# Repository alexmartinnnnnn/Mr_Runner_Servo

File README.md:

# Mr_Runner_Servo

These are two programs which can be used in conjunction to control the Mr. Runner quadrupedal robot.

The code could be modified to control other 8 jointed robots. The required electronics are a
computer, microcontroller, PCB to power servos, and a serial connection.

https://hackaday.io/project/8843-mr-runner

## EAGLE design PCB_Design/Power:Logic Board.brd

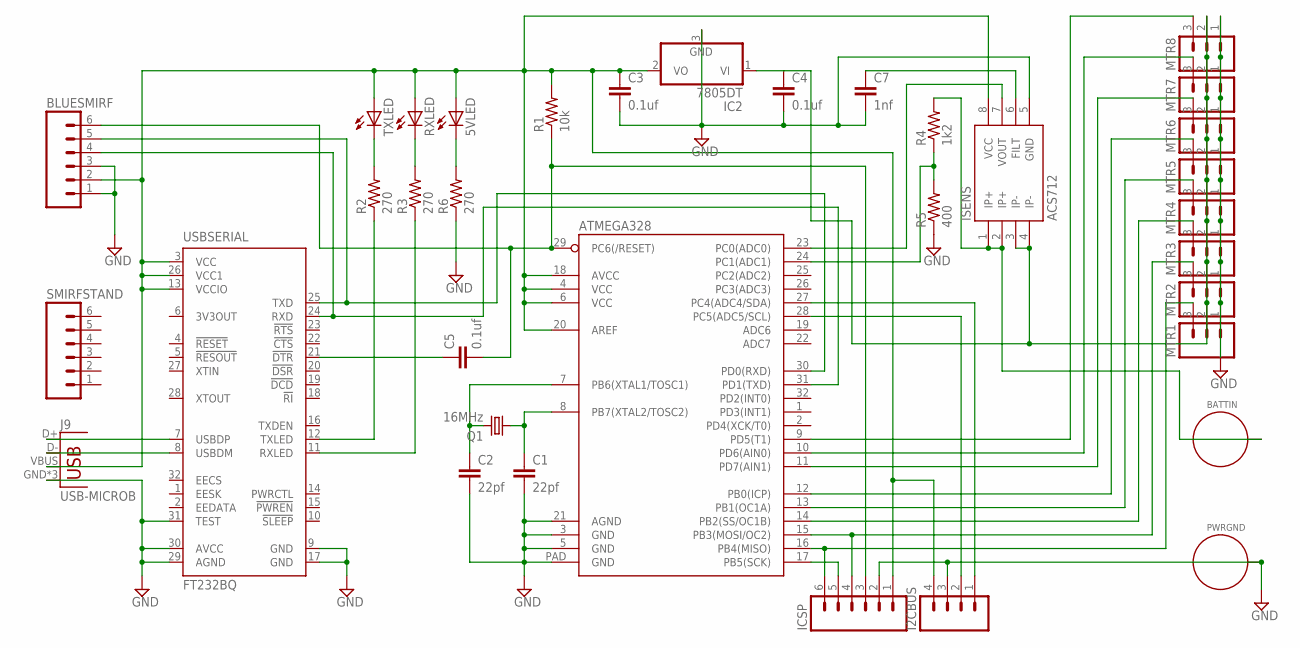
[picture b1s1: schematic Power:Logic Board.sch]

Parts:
5VLED: LEDCHIPLED_0805; CHIPLED_0805
ATMEGA328: ATMEGA328P_MLFMLF32; MLF32-PAD
BATTIN: STANDOFF_ELECTRICAL; STANDOFF-ELECTRICAL
BLUESMIRF: M06NO_SILK_YES_STOP; 1X06_NO_SILK_YES_STOP
C1, C2: 22pf; C0805
C3, C4, C5: 0.1uf; C0805
C7: 1nf; C0805
I2CBUS: M04NO_SILK_ALL_ROUND; 1X04_NO_SILK_ALL_ROUND
IC2: 7805DT; TO252
ICSP: M06NO_SILK_YES_STOP; 1X06_NO_SILK_YES_STOP
ISENS: ACS712; SO08
J9: USB-MICROB
MTR1, MTR2, MTR3, MTR4, MTR5, MTR6, MTR7, MTR8: M03PTH; 1X03
PWRGND: STANDOFF_ELECTRICAL; STANDOFF-ELECTRICAL
Q1: 16MHz; HC49U-V
R1: 10k; 0805
R2, R3, R6: 270; 0805
R4: 1k2; 0805
R5: 400; 0805
RXLED: LEDCHIPLED_0805; CHIPLED_0805
SMIRFSTAND: M06NO_SILK_YES_STOP; 1X06_NO_SILK_YES_STOP
TXLED: LEDCHIPLED_0805; CHIPLED_0805
USBSERIAL: FT232BQ; QFN32

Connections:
GND: ATMEGA328.3 (GND), ATMEGA328.5 (GND), ATMEGA328.21 (AGND), ATMEGA328.PAD (GND), BLUESMIRF.1, BLUESMIRF.3, C1.2, C2.2, C3.2, C4.2, C7.2, I2CBUS.3, IC2.3 (GND), ICSP.2, ISENS.5 (GND), J9.GND, J9.MT1 (GND), J9.MT2 (GND), MTR1.1, MTR2.1, MTR3.1, MTR4.1, MTR5.1, MTR6.1, MTR7.1, MTR8.1, PWRGND.P1, R5.1, R6.1, USBSERIAL.9 (GND), USBSERIAL.17 (GND), USBSERIAL.29 (AGND), USBSERIAL.30 (AVCC), USBSERIAL.31 (TEST)
unnamed: J9.D+, USBSERIAL.7 (USBDP)
unnamed: ATMEGA328.31 (PD1(TXD)), BLUESMIRF.4, USBSERIAL.24 (RXD)
unnamed: J9.D-, USBSERIAL.8 (USBDM)
unnamed: 5VLED.A, ATMEGA328.4 (VCC), ATMEGA328.6 (VCC), ATMEGA328.18 (AVCC), ATMEGA328.20 (AREF), BLUESMIRF.2, C3.1, I2CBUS.4, IC2.2 (VO), ICSP.1, ISENS.8 (VCC), J9.VBUS, R1.2, RXLED.A, TXLED.A, USBSERIAL.3 (VCC), USBSERIAL.13 (VCCIO), USBSERIAL.26 (VCC1)
unnamed: ATMEGA328.14 (PB2(SS/OC1B)), MTR3.3
unnamed: ATMEGA328.23 (PC0(ADC0)), ISENS.7 (VOUT)
unnamed: ATMEGA328.8 (PB7(XTAL2/TOSC2)), C1.1, Q1.1
unnamed: ATMEGA328.9 (PD5(T1)), MTR8.3
unnamed: ATMEGA328.13 (PB1(OC1A)), MTR4.3
unnamed: ATMEGA328.17 (PB5(SCK)), ICSP.5
unnamed: ATMEGA328.12 (PB0(ICP)), MTR5.3
unnamed: ATMEGA328.16 (PB4(MISO)), ICSP.6, MTR1.3
unnamed: ATMEGA328.15 (PB3(MOSI/OC2)), ICSP.4, MTR2.3
unnamed: R2.2, TXLED.C
unnamed: ATMEGA328.7 (PB6(XTAL1/TOSC1)), C2.1, Q1.2
unnamed: R2.1, USBSERIAL.12 (TXLED)
unnamed: R3.2, RXLED.C
unnamed: R3.1, USBSERIAL.11 (RXLED)
unnamed: ATMEGA328.11 (PD7(AIN1)), MTR6.3
unnamed: ATMEGA328.29 (PC6(/RESET)), BLUESMIRF.6, C5.2, ICSP.3, R1.1
unnamed: C7.1, ISENS.6 (FILT)
unnamed: C4.1, IC2.1 (VI), ISENS.3 (IP-), ISENS.4 (IP-), MTR1.2, MTR2.2, MTR3.2, MTR4.2, MTR5.2, MTR6.2, MTR7.2, MTR8.2
unnamed: ATMEGA328.24 (PC1(ADC1)), R4.1, R5.2
unnamed: ATMEGA328.10 (PD6(AIN0)), MTR7.3
unnamed: BATTIN.P1, ISENS.1 (IP+), ISENS.2 (IP+), R4.2
unnamed: ATMEGA328.30 (PD0(RXD)), BLUESMIRF.5, USBSERIAL.25 (TXD)
unnamed: C5.1, USBSERIAL.21 (!DTR)
unnamed: ATMEGA328.28 (PC5(ADC5/SCL)), I2CBUS.2
unnamed: ATMEGA328.27 (PC4(ADC4/SDA)), I2CBUS.1
unnamed: 5VLED.C, R6.2

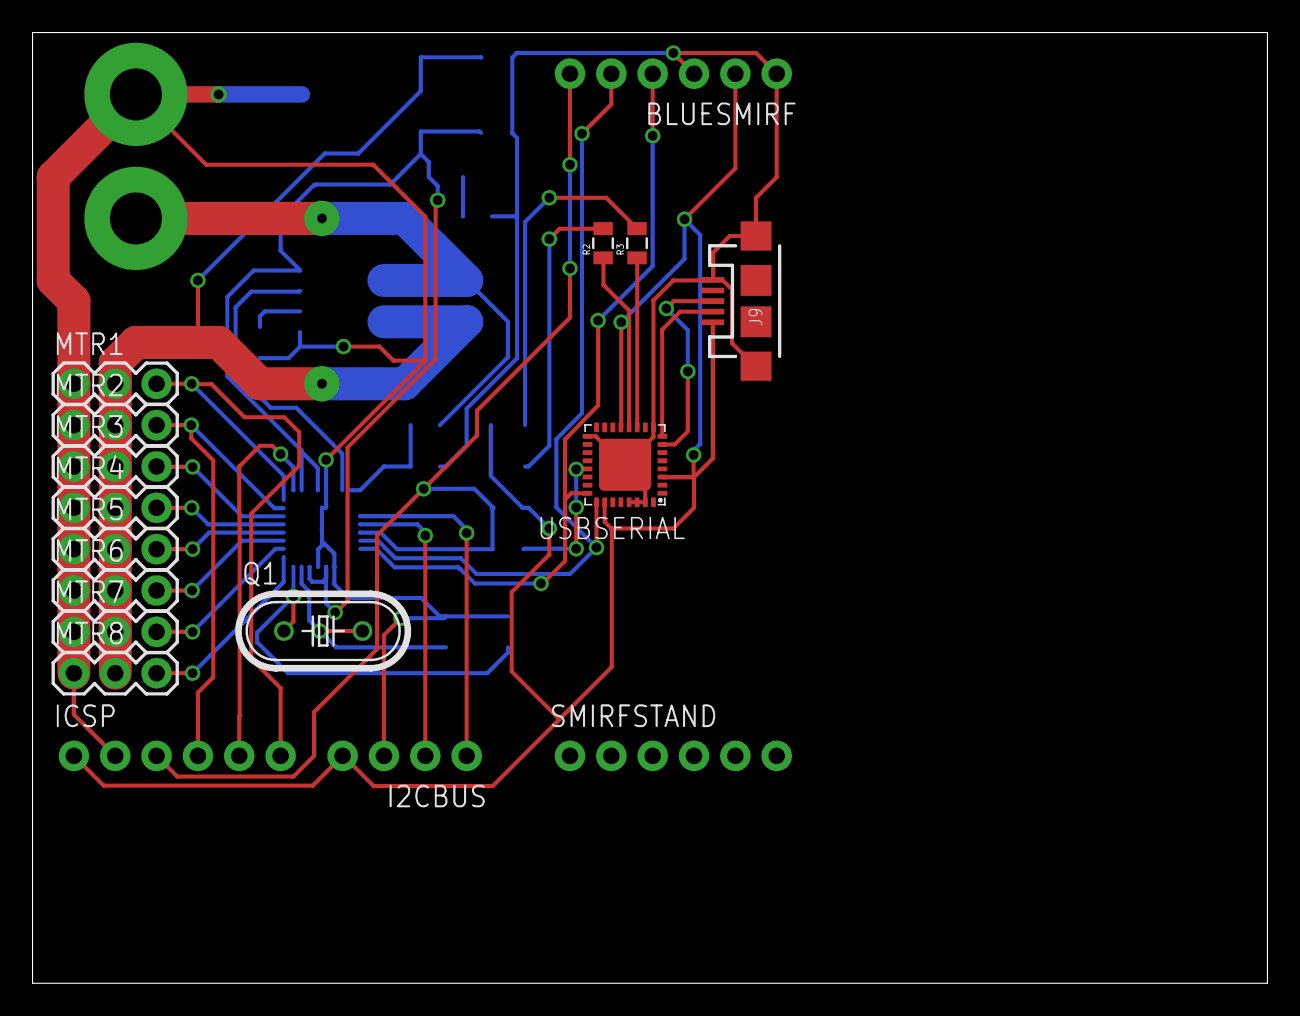
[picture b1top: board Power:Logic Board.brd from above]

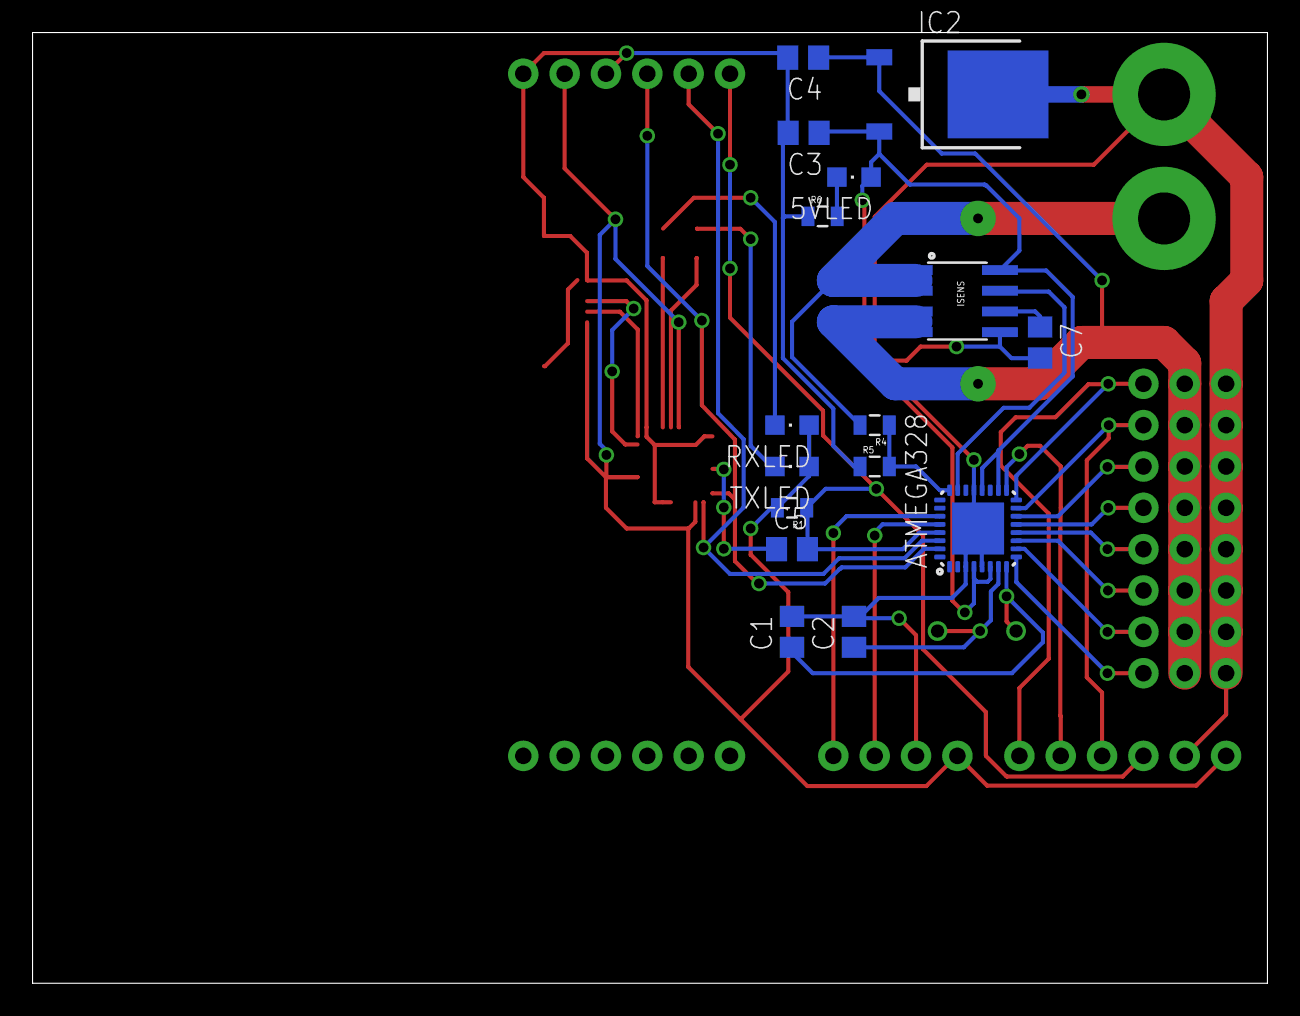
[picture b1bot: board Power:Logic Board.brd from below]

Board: 2 copper layers, 75.9 x 58.4 mm, 35 parts (16 on the bottom side), 31 nets.

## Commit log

2016-01-05 Create Brain.py
    Generates servo positions, controls oscillators from a gui, transmits servo positions via serial.
2016-01-05 Create Spinal_Cord.ino
    Receives servo positions from the brain and relays them to the motors.
2016-01-10 Added Knee Amplitude
2016-01-10 Superficial Changes
2016-01-10 Fixed Indentation
2016-01-10 Small Changes
2016-01-20 Changed afreq param
2016-02-04 New Format
2016-02-06 Now Functional
2016-02-06 Moved variables, added comments
2016-02-06 Bug Fixes
2016-04-05 Added files via upload
2016-09-10 Create ha

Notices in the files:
parts and their libraries:
SparkFun-DigitalIC: Licensing: Creative Commons ShareAlike 4.0 International - https://creativecommons.org/licenses/by-sa/4.0
